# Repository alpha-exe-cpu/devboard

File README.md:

# α EZDEV Devboard
A custom development board based on the RP2040 microcontroller, designed for straightforward prototyping and hardware experimentation.

I designed this Raspberry Pi Pico clone to have a cleaner hardware setup for custom sensor nodes and Home Assistant integrations. It is a fully functional RP2040 development board that runs standard firmware like MicroPython, CircuitPython, and C/C++. For modern convenience, I upgraded the connector to USB Type-C and swapped the standard indicator light for a WS2812B RGB LED.

## Specifications
* **Microcontroller:** RP2040 (Dual-core ARM Cortex-M0+)
* **I/O:** 30 GPIO pins broken out
* **Connector:** USB Type-C
* **Storage:** External QSPI Flash
* **Indicator:** WS2812B-2020 RGB LED connected to GPIO 25

## Firmware Installation
To get CircuitPython running and utilize the onboard NeoPixel, follow these steps:

1. Download the standard Raspberry Pi Pico CircuitPython `.uf2` file from the CircuitPython website.
2. Hold down the BOOTSEL button on the board while plugging it into your computer via USB-C.
3. Copy the downloaded `.uf2` file to the `RPI-RP2` drive that mounts on your computer. The board will automatically reboot and remount as `CIRCUITPY`.
4. Download the Adafruit CircuitPython Library Bundle. Extract the folder, locate the `neopixel.mpy` file, and copy it into the `lib` folder on your new `CIRCUITPY` drive.

## Hardware Design

### PCB Layout

### 3D Renders
**Front**

**Back**

### Schematic

## NeoPixel Usage
Because the standard LED was replaced with a WS2812B NeoPixel, you must drive it as a single-pixel strip on Pin 25.

**CircuitPython Example (`code.py`):**
```python
import board
import neopixel

# Initialize the NeoPixel on GPIO 25
pixel = neopixel.NeoPixel(board.GP25, 1)

# Set the LED to red
pixel.fill((255, 0, 0))
```

## Credits
This project was built following Kai Pierra's guide on Hack Club Blueprint. Check out the original guide here: [Blueprint Starter Project: Devboard](https://blueprint.hackclub.com/starter-projects/devboard)

## Bill of Materials
| Designator | Footprint | Quantity | Value | LCSC Part # |
| :--- | :--- | :--- | :--- | :--- |
| BT1 | PinHeader_1x02_P2.54mm_Vertical | 1 | Battery | DNP |
| C1, C10 | 402 | 2 | 1uF | [C52923](https://www.lcsc.com/search?q=C52923) |
| C11, C12, C17, C2, C3, C4, C5, C6, C7, C8, C9 | 402 | 11 | 0.1uF | [C1525](https://www.lcsc.com/search?q=C1525) |
| C13, C14 | 603 | 2 | 10uF | [C19702](https://www.lcsc.com/search?q=C19702) |
| C15, C16 | 402 | 2 | 33pF | [C1562](https://www.lcsc.com/search?q=C1562) |
| D1 | LED_WS2812B-2020_PLCC4_2.0x2.0mm | 1 | WS2812B-2020 | [C965555](https://www.lcsc.com/search?q=C965555) |
| J1 | USB_C_Receptacle_HRO_TYPE-C-31-M-12 | 1 | USB_C_Receptacle_USB2.0_14P | [C165948](https://www.lcsc.com/search?q=C165948) |
| J2, J3 | PinHeader_1x20_P2.54mm_Vertical | 2 | Conn_01x20 | DNP |
| J4 | PinHeader_1x03_P2.54mm_Vertical | 1 | Conn_01x03 | DNP |
| R1, R2 | 402 | 2 | 5.1K | [C25905](https://www.lcsc.com/search?q=C25905) |
| R3, R4 | 402 | 2 | 27 | [C25100](https://www.lcsc.com/search?q=C25100) |
| R5, R6 | 402 | 2 | 1K | [C11702](https://www.lcsc.com/search?q=C11702) |
| R7 | 402 | 1 | 10K | [C25744](https://www.lcsc.com/search?q=C25744) |
| R8 | 603 | 1 | 470R | [C114669](https://www.lcsc.com/search?q=C114669) |
| R9 | 603 | 1 | 2k | [C22977](https://www.lcsc.com/search?q=C22977) |
| SW1 | SW_Push_SPST_NO_Alps_SKRK | 1 | SW_Push | [C720477](https://www.lcsc.com/search?q=C720477) |
| U1 | QFN-56-1EP_7x7mm_P0.4mm_EP3.2x3.2mm | 1 | RP2040 | [C2040](https://www.lcsc.com/search?q=C2040) |
| U2 | SOT-23 | 1 | MCP1700x-330xxTT | [C39051](https://www.lcsc.com/search?q=C39051) |
| U3 | SOT-23-5 | 1 | MCP73831-2-OT | [C14879](https://www.lcsc.com/search?q=C14879) |
| U4 | Winbond_USON-8-1EP_3x2mm_P0.5mm_EP0.2x1.6mm | 1 | W25Q16JVUXIQ TR | [C2843335](https://www.lcsc.com/search?q=C2843335) |
| Y1 | Crystal_SMD_3225-4Pin_3.2x2.5mm | 1 | 12 MHz | [C9002](https://www.lcsc.com/search?q=C9002) |

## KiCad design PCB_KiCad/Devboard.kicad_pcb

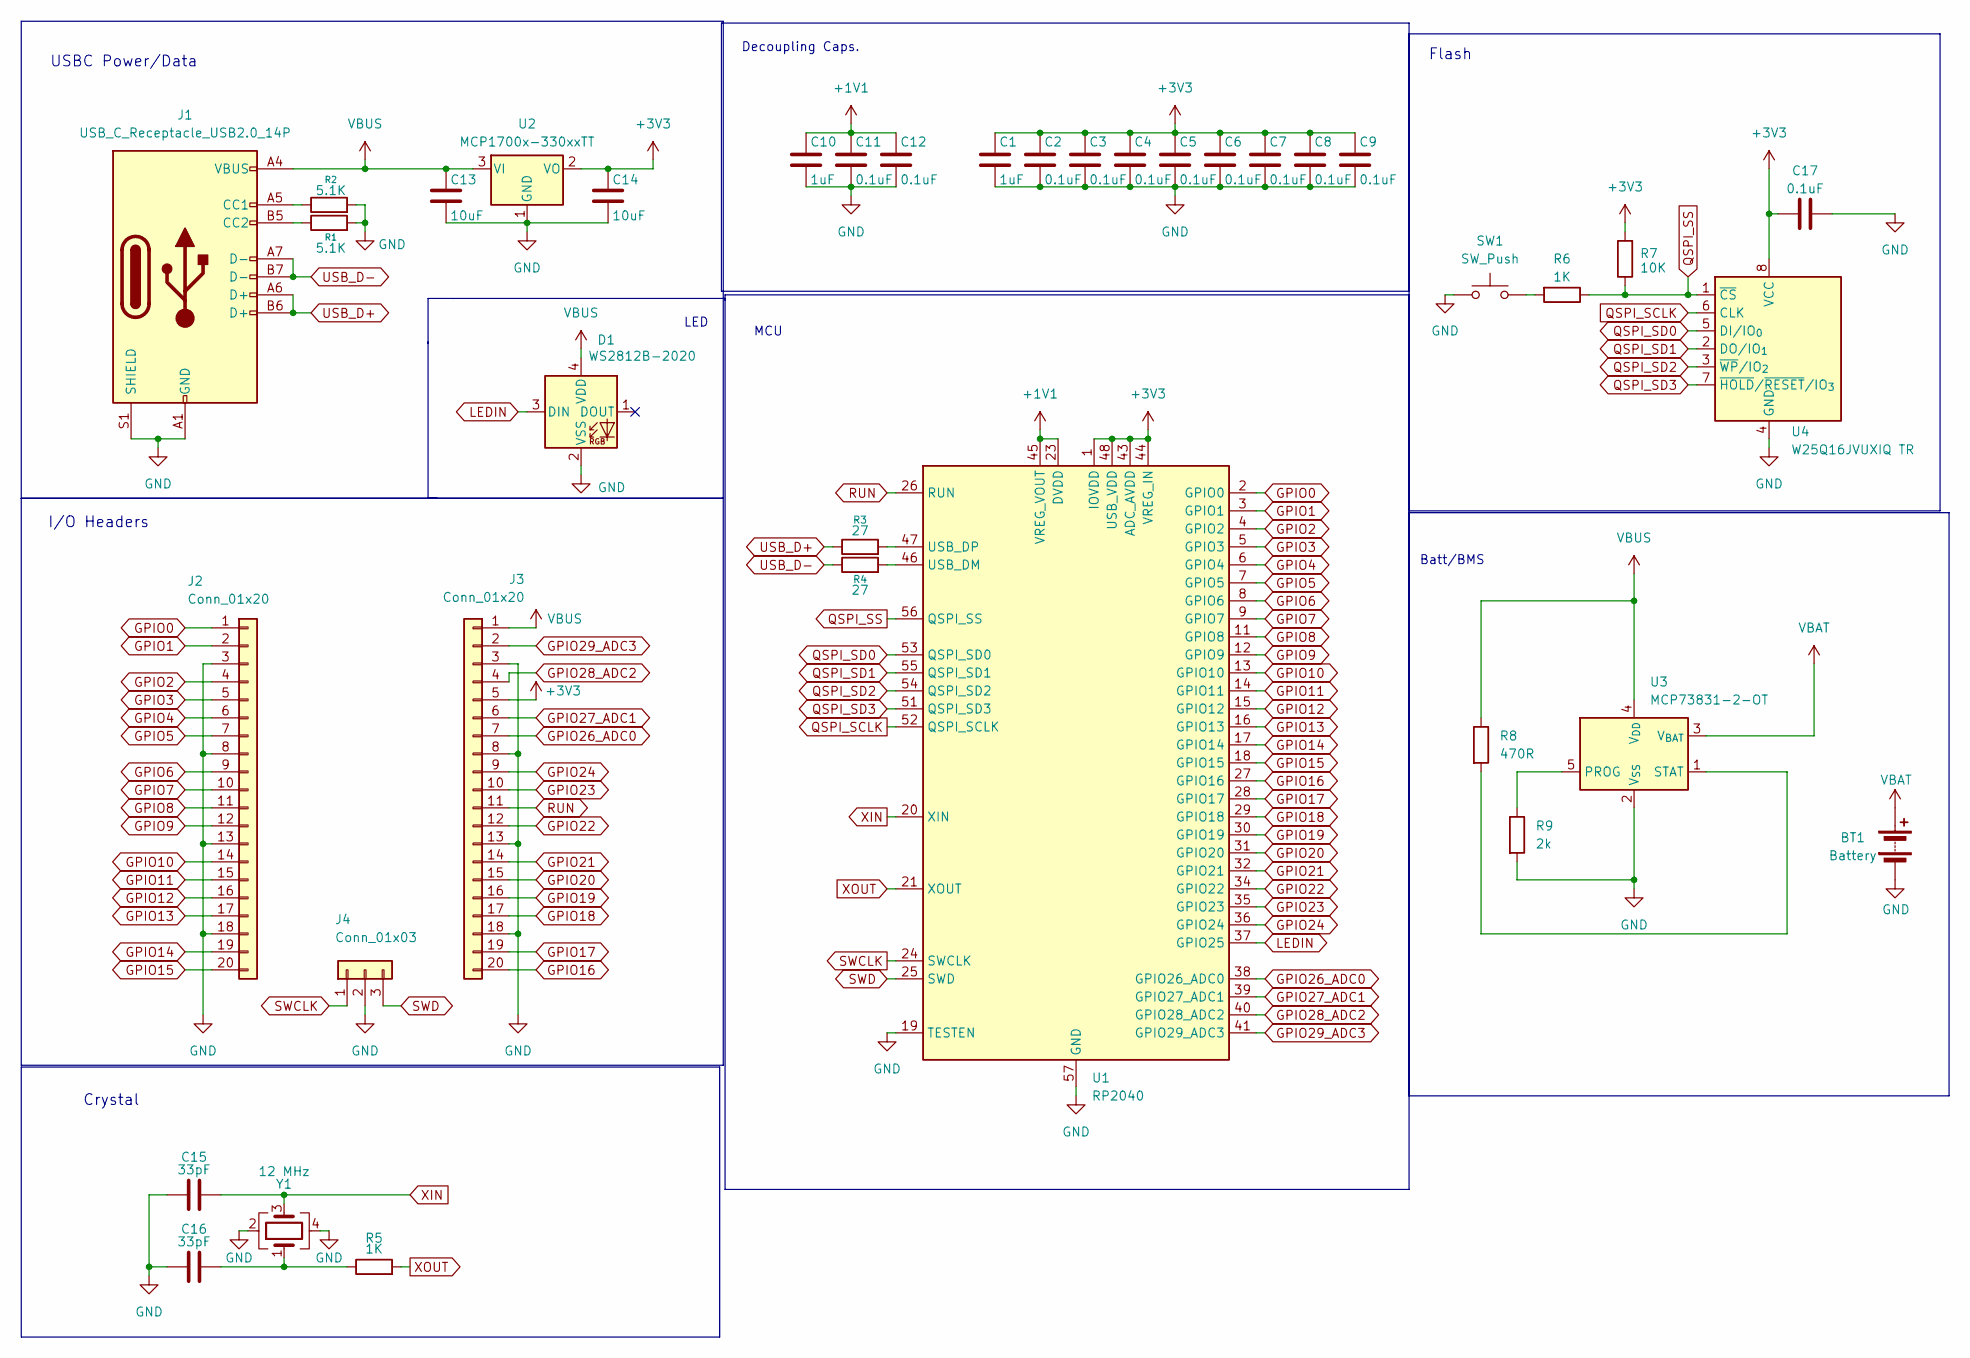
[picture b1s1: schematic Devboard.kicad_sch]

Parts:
BT1: Battery; PinHeader_1x02_P2.54mm_Vertical
C1, C10: 1uF; C_0402_1005Metric
C2, C3, C4, C5, C6, C7, C8, C9, C11, C12, C17: 0.1uF; C_0402_1005Metric
C13, C14: 10uF; C_0603_1608Metric
C15, C16: 33pF; C_0402_1005Metric
D1: WS2812B-2020; LED_WS2812B-2020_PLCC4_2.0x2.0mm
J1: USB_C_Receptacle_USB2.0_14P; USB_C_Receptacle_HRO_TYPE-C-31-M-12
J2, J3: Conn_01x20; PinHeader_1x20_P2.54mm_Vertical
J4: Conn_01x03; PinHeader_1x03_P2.54mm_Vertical
R1, R2: 5.1K; R_0402_1005Metric
R3, R4: 27; R_0402_1005Metric
R5, R6: 1K; R_0402_1005Metric
R7: 10K; R_0402_1005Metric
R8: 470R; R_0603_1608Metric
R9: 2k; R_0603_1608Metric
SW1: SW_Push; SW_Push_SPST_NO_Alps_SKRK
U1: RP2040; QFN-56-1EP_7x7mm_P0.4mm_EP3.2x3.2mm
U2: MCP1700x-330xxTT; SOT-23
U3: MCP73831-2-OT; SOT-23-5
U4: W25Q16JVUXIQ TR; Winbond_USON-8-1EP_3x2mm_P0.5mm_EP0.2x1.6mm
Y1: 12 MHz; Crystal_SMD_3225-4Pin_3.2x2.5mm

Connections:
+1V1: C10.1, C11.1, C12.1, U1.23 (DVDD), U1.45 (VREG_VOUT), U1.50 (DVDD)
+3V3: C1.1, C2.1, C3.1, C4.1, C5.1, C6.1, C7.1, C8.1, C9.1, C14.1, C17.1, J3.5, R7.2, U1.1 (IOVDD), U1.10 (IOVDD), U1.22 (IOVDD), U1.33 (IOVDD), U1.42 (IOVDD), U1.43 (ADC_AVDD), U1.44 (VREG_IN), U1.48 (USB_VDD), U1.49 (IOVDD), U2.2 (VO), U4.8 (VCC)
GND: BT1.2 (-), C1.2, C2.2, C3.2, C4.2, C5.2, C6.2, C7.2, C8.2, C9.2, C10.2, C11.2, C12.2, C13.2, C14.2, C15.1, C16.1, C17.2, D1.2 (VSS), J1.A1 (GND), J1.A12 (GND), J1.B1 (GND), J1.B12 (GND), J1.S1 (SHIELD), J2.3, J2.8, J2.13, J2.18, J3.3, J3.8, J3.13, J3.18, J4.2, R1.2, R2.2, R9.2, SW1.1, U1.19 (TESTEN), U1.57 (GND), U2.1 (GND), U3.2 (V_{SS}), U4.4 (GND), Y1.2, Y1.4
GPIO0: J2.1, U1.2 (GPIO0)
GPIO1: J2.2, U1.3 (GPIO1)
GPIO2: J2.4, U1.4 (GPIO2)
GPIO3: J2.5, U1.5 (GPIO3)
GPIO4: J2.6, U1.6 (GPIO4)
GPIO5: J2.7, U1.7 (GPIO5)
GPIO6: J2.9, U1.8 (GPIO6)
GPIO7: J2.10, U1.9 (GPIO7)
GPIO8: J2.11, U1.11 (GPIO8)
GPIO9: J2.12, U1.12 (GPIO9)
GPIO10: J2.14, U1.13 (GPIO10)
GPIO11: J2.15, U1.14 (GPIO11)
GPIO12: J2.16, U1.15 (GPIO12)
GPIO13: J2.17, U1.16 (GPIO13)
GPIO14: J2.19, U1.17 (GPIO14)
GPIO15: J2.20, U1.18 (GPIO15)
GPIO16: J3.20, U1.27 (GPIO16)
GPIO17: J3.19, U1.28 (GPIO17)
GPIO18: J3.17, U1.29 (GPIO18)
GPIO19: J3.16, U1.30 (GPIO19)
GPIO20: J3.15, U1.31 (GPIO20)
GPIO21: J3.14, U1.32 (GPIO21)
GPIO22: J3.12, U1.34 (GPIO22)
GPIO23: J3.10, U1.35 (GPIO23)
GPIO24: J3.9, U1.36 (GPIO24)
GPIO26_ADC0: J3.7, U1.38 (GPIO26_ADC0)
GPIO27_ADC1: J3.6, U1.39 (GPIO27_ADC1)
GPIO28_ADC2: J3.4, U1.40 (GPIO28_ADC2)
GPIO29_ADC3: J3.2, U1.41 (GPIO29_ADC3)
LEDIN: D1.3 (DIN), U1.37 (GPIO25)
unnamed: C16.2, R5.1, Y1.1
unnamed: J1.A5 (CC1), R2.1
unnamed: J1.B5 (CC2), R1.1
unnamed: R6.2, SW1.2
unnamed: R4.2, U1.46 (USB_DM)
unnamed: R3.2, U1.47 (USB_DP)
unnamed: R9.1, U3.5 (PROG)
unnamed: R8.2, U3.1 (STAT)
QSPI_SCLK: U1.52 (QSPI_SCLK), U4.6 (CLK)
QSPI_SD0: U1.53 (QSPI_SD0), U4.5 (DI/IO_{0})
QSPI_SD1: U1.55 (QSPI_SD1), U4.2 (DO/IO_{1})
QSPI_SD2: U1.54 (QSPI_SD2), U4.3 (~WP/IO_{2})
QSPI_SD3: U1.51 (QSPI_SD3), U4.7 (~HOLD/~RESET/IO_{3})
QSPI_SS: R6.1, R7.1, U1.56 (QSPI_SS), U4.1 (~CS)
RUN: J3.11, U1.26 (RUN)
SWCLK: J4.1, U1.24 (SWCLK)
SWD: J4.3, U1.25 (SWD)
USB_D+: J1.A6 (D+), J1.B6 (D+), R3.1
USB_D-: J1.A7 (D-), J1.B7 (D-), R4.1
VBAT: BT1.1 (+), U3.3 (V_{BAT})
VBUS: C13.1, D1.4 (VDD), J1.A4 (VBUS), J1.A9 (VBUS), J1.B4 (VBUS), J1.B9 (VBUS), J3.1, R8.1, U2.3 (VI), U3.4 (V_{DD})
XIN: C15.2, U1.20 (XIN), Y1.3
XOUT: R5.2, U1.21 (XOUT)

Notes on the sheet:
Flash
I/O Headers
Decoupling Caps.
LED
MCU
Batt/BMS
Crystal
USBC Power/Data

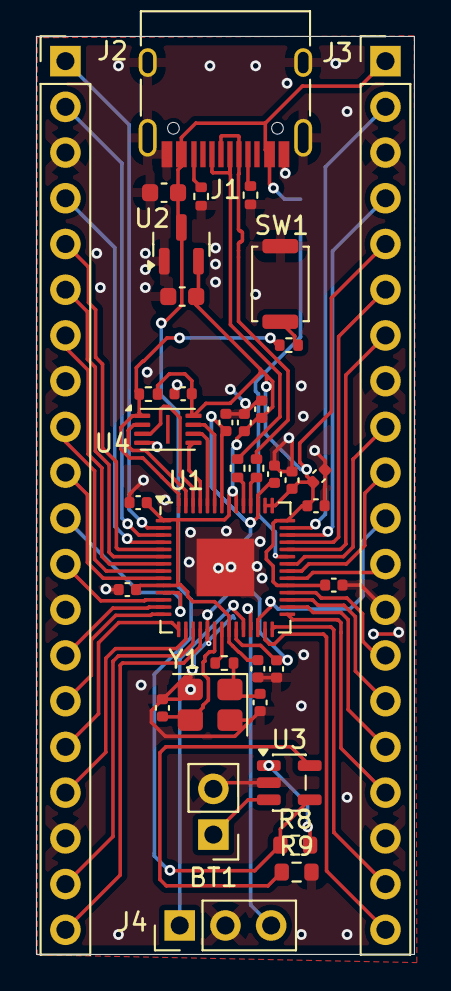
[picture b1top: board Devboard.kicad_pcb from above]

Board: 2 copper layers, 21.0 x 51.0 mm, 38 parts (1 on the bottom side), 56 nets.

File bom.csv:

Designator,Footprint,Quantity,Value,LCSC Part #
BT1,PinHeader_1x02_P2.54mm_Vertical,1,Battery,DNP
"C1, C10",402,2,1uF,C52923
"C11, C12, C17, C2, C3, C4, C5, C6, C7, C8, C9",402,11,0.1uF,C1525
"C13, C14",603,2,10uF,C19702
"C15, C16",402,2,33pF,C1562
D1,LED_WS2812B-2020_PLCC4_2.0x2.0mm,1,WS2812B-2020,C965555
J1,USB_C_Receptacle_HRO_TYPE-C-31-M-12,1,USB_C_Receptacle_USB2.0_14P,C165948
"J2, J3",PinHeader_1x20_P2.54mm_Vertical,2,Conn_01x20,DNP
J4,PinHeader_1x03_P2.54mm_Vertical,1,Conn_01x03,DNP
"R1, R2",402,2,5.1K,C25905
"R3, R4",402,2,27,C25100
"R5, R6",402,2,1K,C11702
R7,402,1,10K,C25744
R8,603,1,470R,C114669
R9,603,1,2k,C22977
SW1,SW_Push_SPST_NO_Alps_SKRK,1,SW_Push,C720477
U1,QFN-56-1EP_7x7mm_P0.4mm_EP3.2x3.2mm,1,RP2040,C2040
U2,SOT-23,1,MCP1700x-330xxTT,C39051
U3,SOT-23-5,1,MCP73831-2-OT,C14879
U4,Winbond_USON-8-1EP_3x2mm_P0.5mm_EP0.2x1.6mm,1,W25Q16JVUXIQ TR,C2843335
Y1,Crystal_SMD_3225-4Pin_3.2x2.5mm,1,12 MHz,C9002

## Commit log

2026-04-18 Rename journal.md to JOURNAL.md
